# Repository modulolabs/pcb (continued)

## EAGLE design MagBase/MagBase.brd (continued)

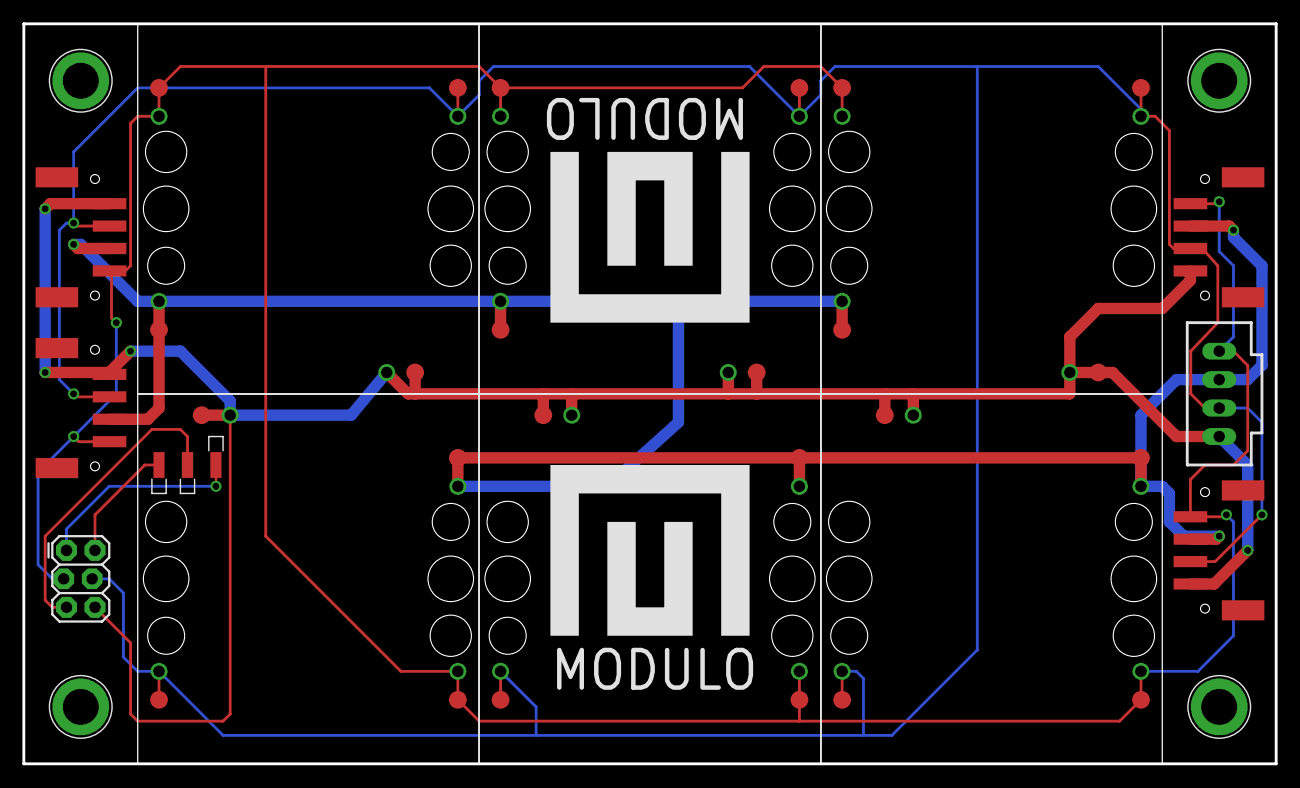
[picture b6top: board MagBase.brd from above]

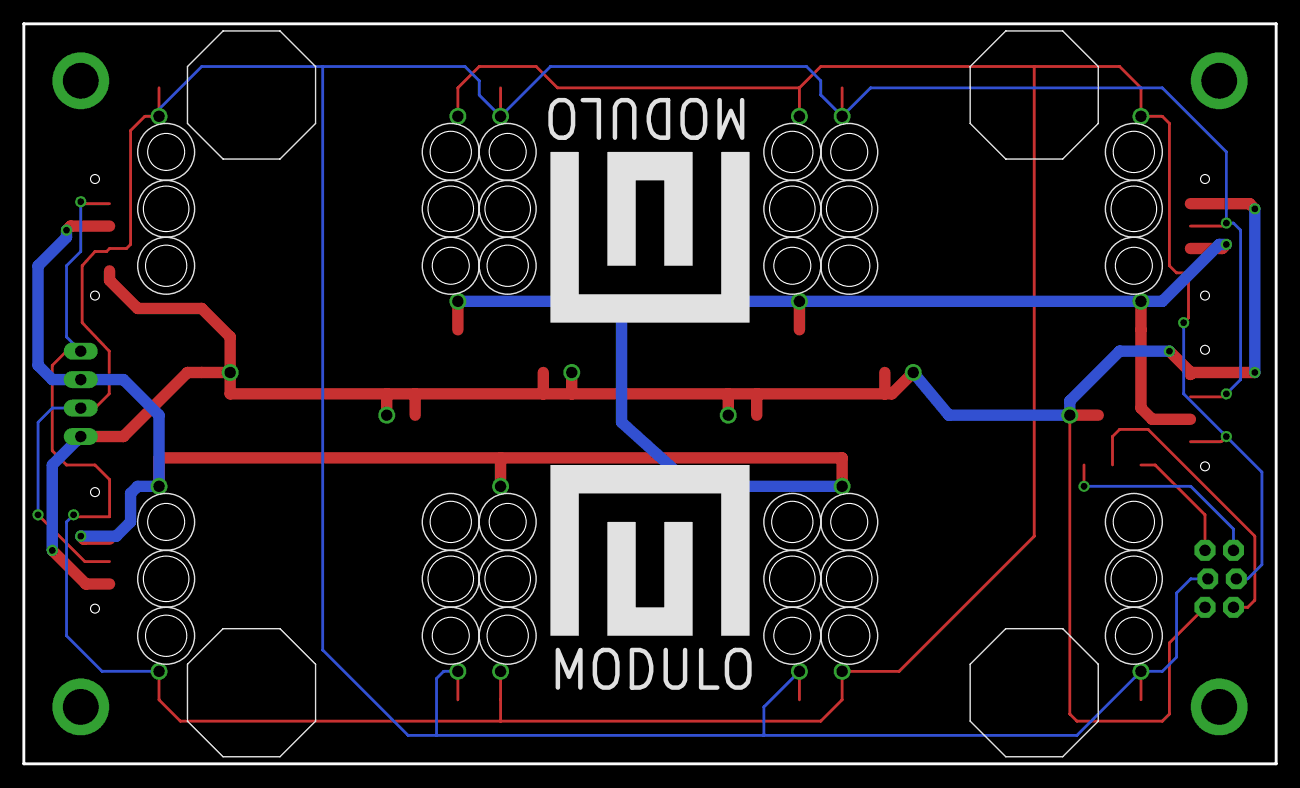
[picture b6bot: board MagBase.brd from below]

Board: 2 copper layers, 111.8 x 66.0 mm, 23 parts (4 on the bottom side), 7 nets.

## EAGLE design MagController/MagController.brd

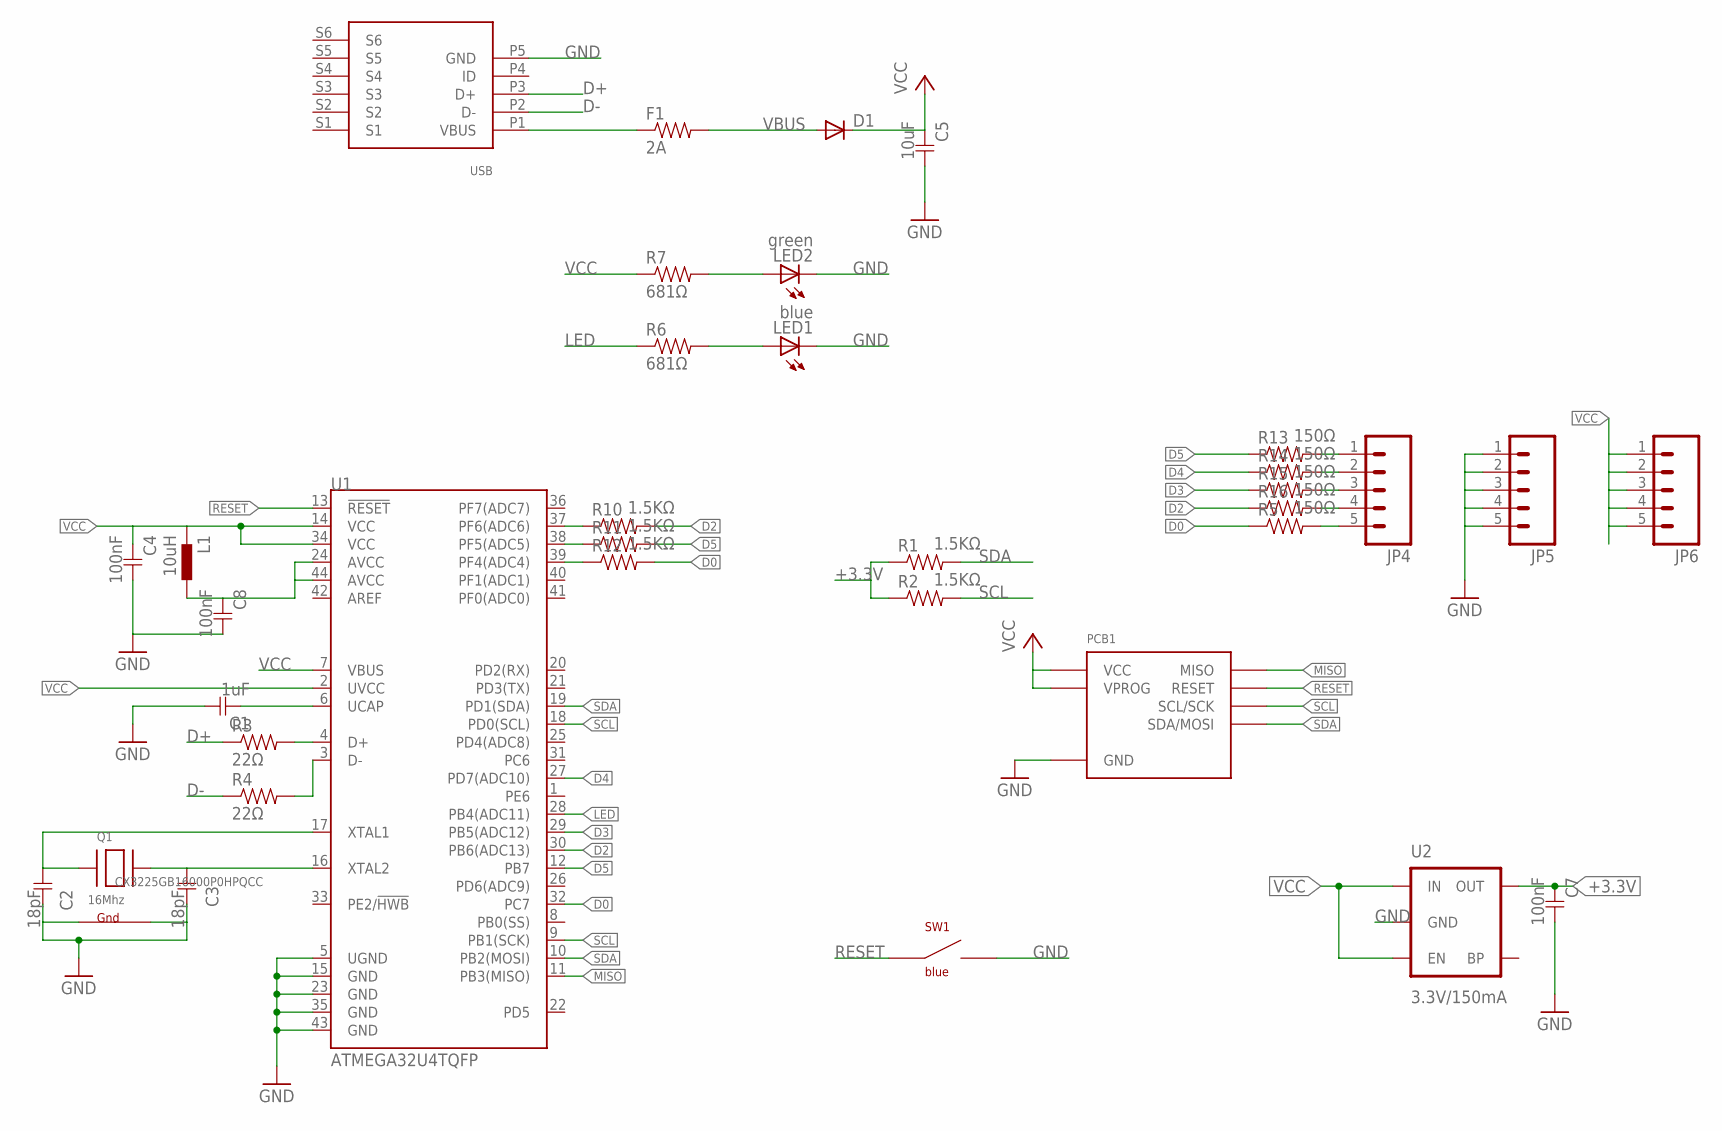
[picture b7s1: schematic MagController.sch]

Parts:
C1: 1uF; 0603
C2, C3: 18pF; 0603
C4, C7, C8: 100nF; 0603
C5: 10uF; 0603
D1: DIODESMA; SMA-DIODE; PARTNUM SSA33L-E3/61TGICT-ND
F1: 2A; 0603; PARTNUM MF-PSMF110X-2
JP4, JP5, JP6: M05NO_SILK; 1X05_NO_SILK
L1: 10uH; 0603
LED1: blue; 0805-LED
LED2: green; 0805-LED
PCB1: MAGDEVICE
Q1: 16Mhz; NX3225; PARTNUM CX3225GB16000P0HPQCC
R1, R2, R10, R11, R12: 1.5KΩ; 0603
R3, R4: 22Ω; 0603
R5, R13, R14, R15, R16: 150Ω; 0603
R6, R7: 681Ω; 0603
SW1: blue; BOURNS-7914J
U1: ATMEGA32U4TQFP; SPARKFUN-DIGITALIC_TQFP44; PARTNUM ATMEGA32U4-AU
U2: 3.3V/150mA; SOT23-5; PARTNUM MIC5205-3.3YM5 TR
U3: USBFCI-MICROB; USB-MICROB-FCI; PARTNUM 10118194-0001LF

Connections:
+3.3V: C7.1, R1.1, R2.1, U2.5 (OUT)
AVCC: C8.1, L1.2, U1.24 (AVCC), U1.44 (AVCC)
D0: R5.1, R12.2, U1.32 (PC7)
D2: R10.2, R16.1, U1.30 (PB6(ADC13))
D3: R15.1, U1.29 (PB5(ADC12))
D4: R14.1, U1.27 (PD7(ADC10))
D5: R11.2, R13.1, U1.12 (PB7)
D+: R3.1, U3.P3 (D+)
D-: R4.1, U3.P2 (D-)
GND: C1.2, C2.2, C3.2, C4.2, C5.2, C7.2, C8.2, JP5.1, JP5.2, JP5.3, JP5.4, JP5.5, LED1.C, LED2.C, PCB1.GNDA (GND), PCB1.GNDB (GND), Q1.2 (G1), Q1.4 (G2), SW1.NEG$1 (NEG1), SW1.NEG$2 (NEG1), U1.5 (UGND), U1.15 (GND), U1.23 (GND), U1.35 (GND), U1.43 (GND), U2.2 (GND), U3.P5 (GND)
LED: R6.1, U1.28 (PB4(ADC11))
MISO: PCB1.MISO, U1.11 (PB3(MISO))
unnamed: C1.1, U1.6 (UCAP)
unnamed: JP4.1, R13.2
unnamed: F1.1, U3.P1 (VBUS)
unnamed: C3.1, Q1.3 (X2), U1.16 (XTAL2)
unnamed: LED1.A, R6.2
unnamed: R12.1, U1.39 (PF4(ADC4))
unnamed: R11.1, U1.38 (PF5(ADC5))
unnamed: R3.2, U1.4 (D+)
unnamed: R4.2, U1.3 (D-)
unnamed: R10.1, U1.37 (PF6(ADC6))
unnamed: JP4.5, R5.2
unnamed: LED2.A, R7.2
unnamed: JP4.2, R14.2
unnamed: C2.1, Q1.1 (X1), U1.17 (XTAL1)
unnamed: JP4.3, R15.2
unnamed: JP4.4, R16.2
RESET: PCB1.RESET, SW1.POS$1 (POS1), SW1.POS$2 (POS1), U1.13 (!RESET)
SCL: PCB1.SCLA (SCL/SCK), PCB1.SCLB (SCL/SCK), R2.2, U1.9 (PB1(SCK)), U1.18 (PD0(SCL))
SDA: PCB1.SDAA (SDA/MOSI), PCB1.SDAB (SDA/MOSI), R1.2, U1.10 (PB2(MOSI)), U1.19 (PD1(SDA))
VBUS: D1.A, F1.2
VCC: C4.1, C5.1, D1.C, JP6.1, JP6.2, JP6.3, JP6.4, JP6.5, L1.1, PCB1.VCCA (VCC), PCB1.VCCB (VCC), PCB1.VPROG, R7.1, U1.2 (UVCC), U1.7 (VBUS), U1.14 (VCC), U1.34 (VCC), U2.1 (IN), U2.3 (EN)

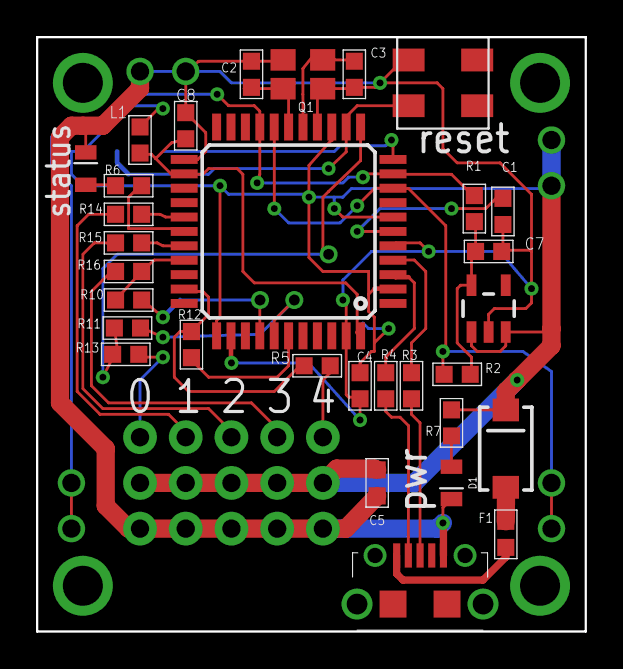
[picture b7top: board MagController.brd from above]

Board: 2 copper layers, 30.5 x 33.0 mm, 35 parts (0 on the bottom side), 33 nets.

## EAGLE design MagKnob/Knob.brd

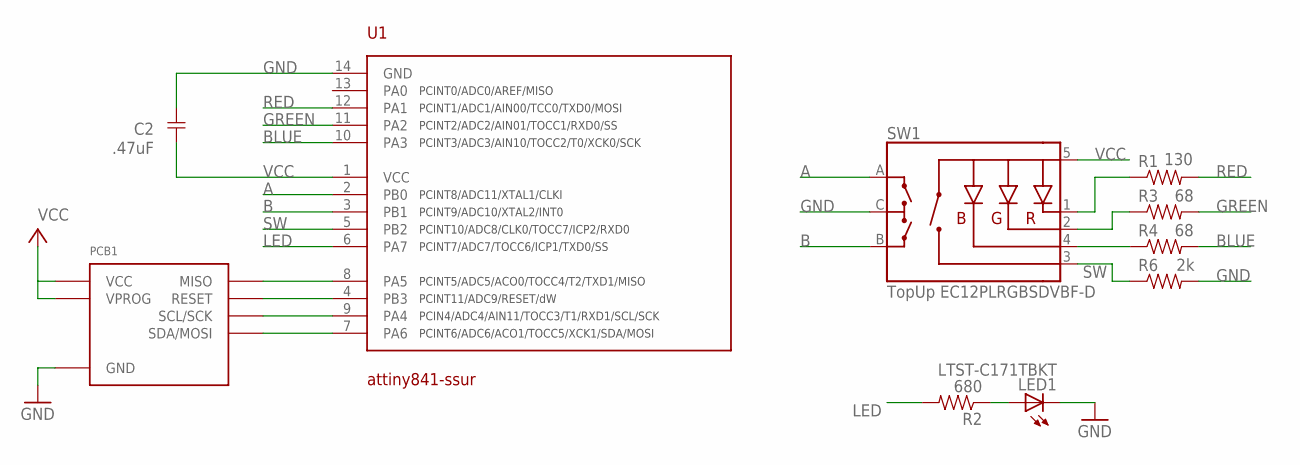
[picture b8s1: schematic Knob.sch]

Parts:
C2: .47uF; 0805
LED1: LTST-C171TBKT; 0805-LED
PCB1: MAGDEVICE
R1: 130; 0805
R2: 680; 0805
R3, R4: 68; 0805
R6: 2k; 0805
SW1: TopUp EC12PLRGBSDVBF-D; ENCODER_LED_3
U1: attiny841-ssur; SOIC14

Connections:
A: SW1.A, U1.2 (PB0)
B: SW1.B, U1.3 (PB1)
BLUE: R4.2, U1.10 (PA3)
GND: C2.2, LED1.C, PCB1.GNDA (GND), PCB1.GNDB (GND), R6.2, SW1.C, U1.14 (GND)
GREEN: R3.2, U1.11 (PA2)
LED: R2.2, U1.6 (PA7)
MISO: PCB1.MISO, U1.8 (PA5)
unnamed: R1.1, SW1.1 (-R)
unnamed: R3.1, SW1.2 (-G)
unnamed: R4.1, SW1.4 (-B)
unnamed: LED1.A, R2.1
RED: R1.2, U1.12 (PA1)
RESET: PCB1.RESET, U1.4 (PB3)
SCL/SCK: PCB1.SCLA (SCL/SCK), PCB1.SCLB (SCL/SCK), U1.9 (PA4)
SDA/MOSI: PCB1.SDAA (SDA/MOSI), PCB1.SDAB (SDA/MOSI), U1.7 (PA6)
SW: R6.1, SW1.3 (SW), U1.5 (PB2)
VCC: C2.1, PCB1.VCCA (VCC), PCB1.VCCB (VCC), PCB1.VPROG, SW1.5 (+), U1.1 (VCC)

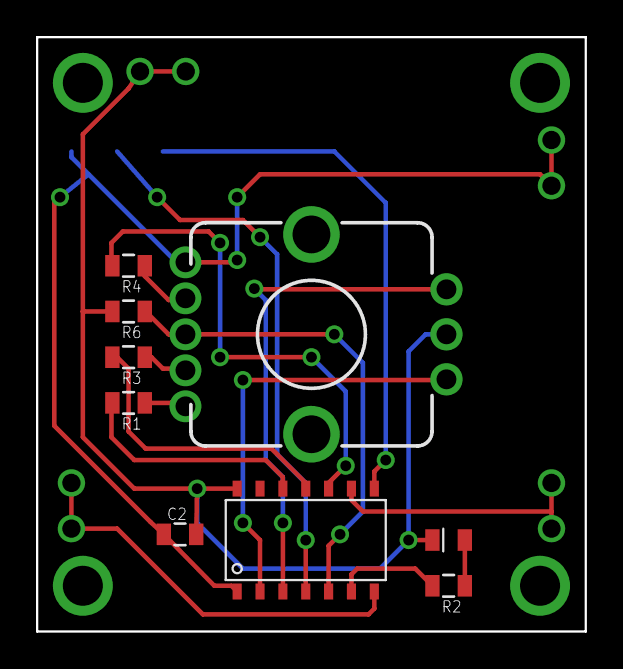
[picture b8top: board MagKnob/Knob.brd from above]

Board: 2 copper layers, 30.5 x 33.0 mm, 10 parts (0 on the bottom side), 17 nets.
